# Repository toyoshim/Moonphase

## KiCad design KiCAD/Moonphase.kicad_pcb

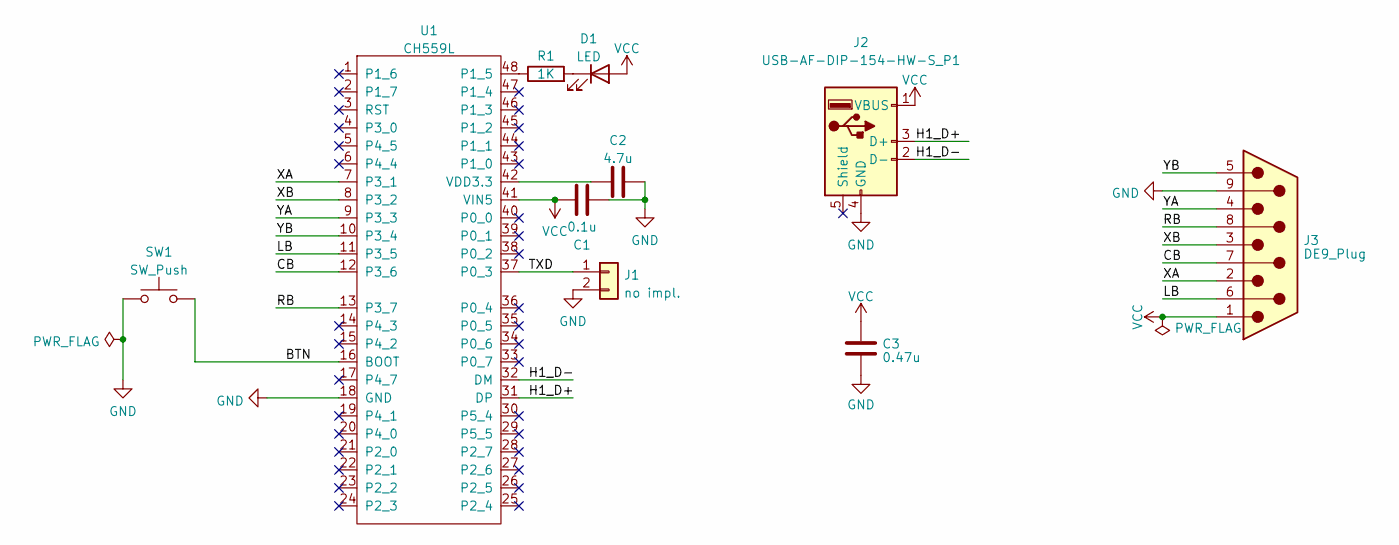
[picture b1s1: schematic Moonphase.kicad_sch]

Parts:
C1: 0.1u; C_0402_1005Metric
C2: 4.7u; C_0402_1005Metric
C3: 0.47u; C_0402_1005Metric
D1: LED; LED_0603_1608Metric_Pad1.05x0.95mm_HandSolder; LCSC C965807
J1: no impl.; PinHeader_2x01_P2.54mm_Vertical
J2: USB-AF-DIP-154-HW-S_P1; USB-A-TH_JTJ-USB-A-F-10.0-010; LCSC C42576
J3: DE9_Plug; DSUB-9P-Male-FOXCONN_DT10121; LCSC C426221
R1: 1K; R_0402_1005Metric
SW1: SW_Push; TS-1159B; LCSC C381055
U1: CH559L; LQFP-48_7x7mm_P0.5mm; LCSC C150548

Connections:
/BTN: SW1.2, U1.16 (BOOT)
/CB: J3.7, U1.12 (P3_6)
/H1_D+: J2.3 (D+), U1.31 (DP)
/H1_D-: J2.2 (D-), U1.32 (DM)
/LB: J3.6, U1.11 (P3_5)
/RB: J3.8, U1.13 (P3_7)
/TXD: J1.1, U1.37 (P0_3)
/XA: J3.2, U1.7 (P3_1)
/XB: J3.3, U1.8 (P3_2)
/YA: J3.4, U1.9 (P3_3)
/YB: J3.5, U1.10 (P3_4)
GND: C1.2, C2.2, C3.2, J1.2, J2.4 (GND), J3.9, SW1.1, U1.18 (GND)
unnamed: D1.1 (K), R1.2
unnamed: R1.1, U1.48 (P1_5)
unnamed: C2.1, U1.42 (VDD3.3)
VCC: C1.1, C3.1, D1.2 (A), J2.1 (VBUS), J3.1, U1.41 (VIN5)

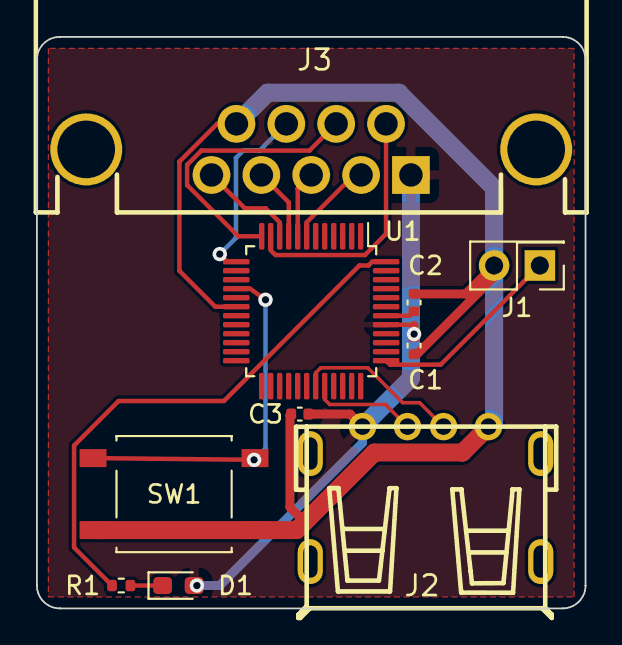
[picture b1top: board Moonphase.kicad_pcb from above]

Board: 2 copper layers, 30.5 x 31.8 mm, 10 parts (0 on the bottom side), 16 nets.

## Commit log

2024-01-26 KiCad data
2024-01-26 add chlib
2024-01-26 firmware works
